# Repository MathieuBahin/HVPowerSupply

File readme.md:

# High Voltage Power Supply

## From 129.7V to 348.0V DC
[Based on the NK02 of Threeneuron's HV Supply Kit](https://threeneurons.wordpress.com/nixie-power-supply/hv-supply-kit/).

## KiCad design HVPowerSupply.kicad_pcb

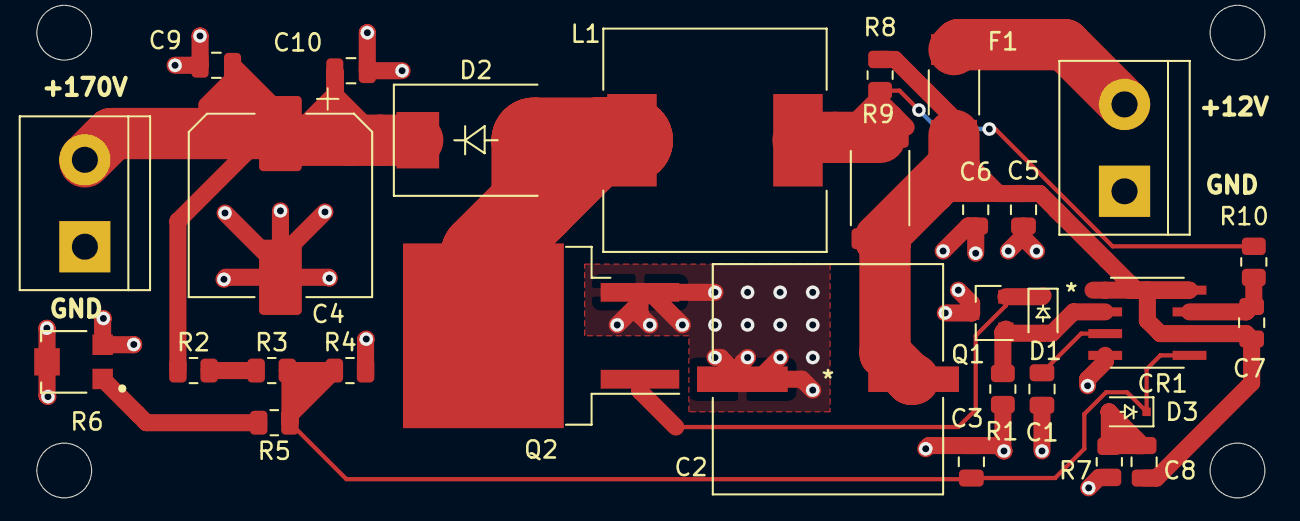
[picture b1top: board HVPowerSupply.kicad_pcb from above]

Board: 2 copper layers, 34 parts (0 on the bottom side), 14 nets.

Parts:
C1: 680p 50V; C_0805_2012Metric
C2: 680u; 35TRV680M12_5X16
C3: 0.01u; C_0805_2012Metric
C4: 2.2u 400V; CP_Elec_10x10.5
C5, C6, C9, C10: 100n; C_0805_2012Metric
C7: 330p; C_0805_2012Metric
C8: 10n; C_0805_2012Metric
CR1: MC34063ACD-TR
D1, D3: 1N914; D_SOD-323F
D2: ES3J; D_SMC
F1: 2A 125V; 0451002_MRL
H1, H2, H3, H4: M3; MountingHole_3.2mm_M3
J1: Input; bornier-2_P5.08mm
J2: Output; bornier-2_P5.08mm
L1: 100uH 2.1A; SRR1280-100M
Q1: SST2907AHZGT116
Q2: IRF740; TO-263-2
R1: 1k; R_0805_2012Metric
R2: 475k; R_0805_2012Metric
R3: 392k; R_0805_2012Metric
R4: 13.7k; R_0805_2012Metric
R5: 4.02k; R_0805_2012Metric
R6: TC33X-2-203E
R7: 10k; R_0805_2012Metric
R8: 1; R_0805_2012Metric
R9: 0,22; R_2512_6332Metric
R10: 100; R_0805_2012Metric

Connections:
+12V: C2.1, C5.1, C6.1, C7.1, C8.1, CR1.1, CR1.6, CR1.8, F1.1, R8.1, R9.2
CII: C3.1, CR1.5, D3.1, R3.2, R4.1, R5.1
GND: C1.2, C2.2, C3.2, C4.2, C5.2, C6.2, C9.2, C10.2, CR1.4, J1.1, J2.1, Q1.3, Q2.3, R1.2, R4.2, R6.2, R6.3, R7.2
IPX: C7.2, CR1.7, R10.2
unnamed: C1.1, CR1.3
unnamed: C8.2, D3.2, R7.1
unnamed: C4.1, C9.1, C10.1, D2.1, J2.2, R2.1
unnamed: D1.1, Q1.1, Q2.1
unnamed: D2.2, L1.2, Q2.2
unnamed: F1.2, J1.2
unnamed: L1.1, R8.2, R9.1, R10.1
unnamed: R2.2, R3.1
unnamed: R5.2, R6.1
SWE: CR1.2, D1.2, Q1.2, R1.1

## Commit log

2022-04-01 First revision : from 129.7V to 348.0V DC
2022-04-01 added images
2022-04-01 NK02

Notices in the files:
parts and their libraries:
Copyright 2021 Accelerated Designs. All rights reserved.
